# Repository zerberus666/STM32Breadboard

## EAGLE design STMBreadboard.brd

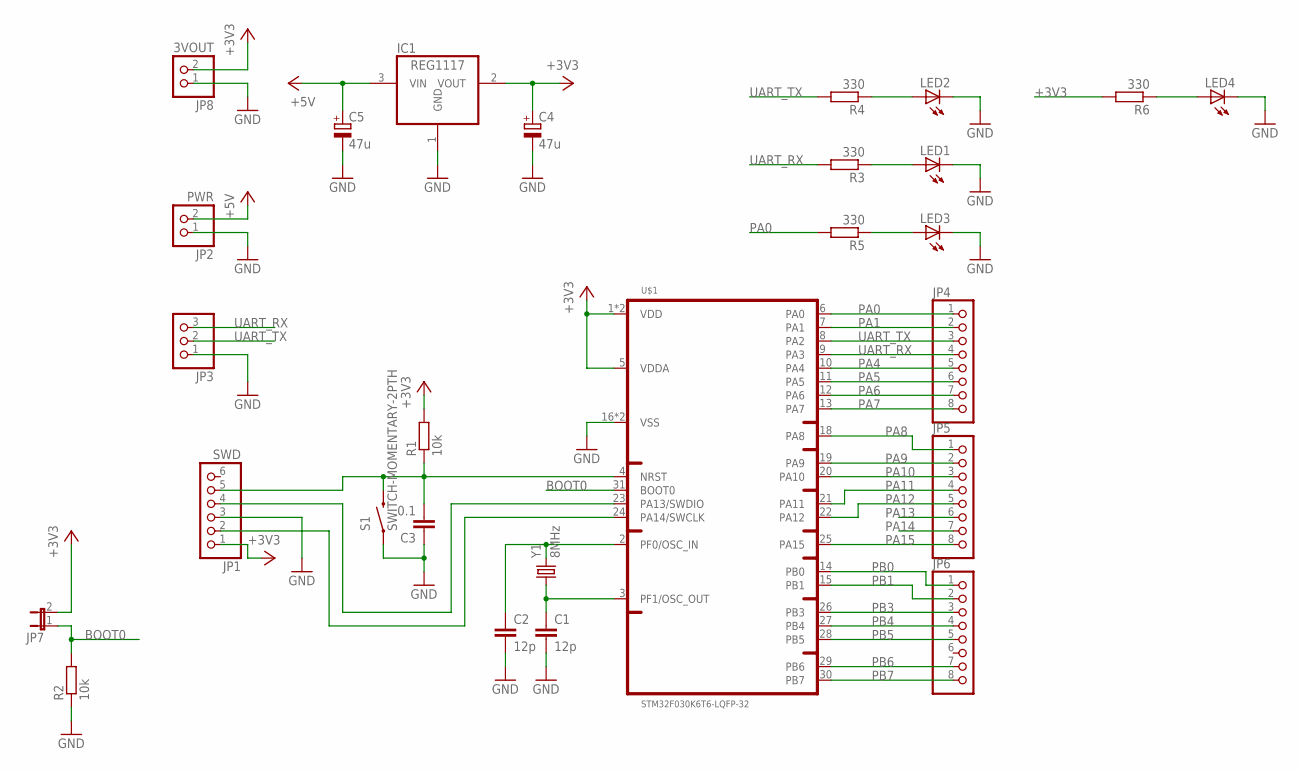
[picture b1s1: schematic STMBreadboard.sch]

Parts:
C1, C2: 12p; C0805
C3: 0.1; C0805
C4, C5: 47u; UD-6,3X7,7_NICHICON
IC1: REG1117; SOT223
JP1: SWD; 1X06
JP2: PWR; 1X02
JP3: PINHD-1X3; 1X03
JP4, JP5, JP6: PINHD-1X8; 1X08
JP7: JP1E; JP1
JP8: 3VOUT; 1X02
LED1, LED2: LEDCHIPLED_0603; CHIPLED_0603
LED3, LED4: LEDSML0603; SML0603
R1, R2: 10k; R1206
R3, R4, R5, R6: 330; R1206
S1: SWITCH-MOMENTARY-2PTH; TACTILE-PTH
U$1: STM32F030K6T6-LQFP-32; LQFP-32
Y1: 8MHz; HC49UP

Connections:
+3V3: C4.+, IC1.2 (VOUT), JP1.1, JP7.2, JP8.2, R1.2, R6.2, U$1.1 (VDD), U$1.5 (VDDA), U$1.17 (VDD)
+5V: C5.+, IC1.3 (VIN), JP2.2
BOOT0: JP7.1, R2.2, U$1.31 (BOOT0)
GND: C1.2, C2.2, C3.1, C4.-, C5.-, IC1.1 (GND), JP1.3, JP2.1, JP3.1, JP8.1, LED1.C, LED2.C, LED3.C, LED4.C, R2.1, S1.1, U$1.16 (VSS), U$1.32 (VSS)
unnamed: C2.1, U$1.2 (PF0/OSC_IN), Y1.2
unnamed: C1.1, U$1.3 (PF1/OSC_OUT), Y1.1
unnamed: C3.2, JP1.5, R1.1, S1.3 (2), U$1.4 (NRST)
unnamed: LED1.A, R3.1
unnamed: LED2.A, R4.1
unnamed: LED3.A, R5.1
unnamed: LED4.A, R6.1
PA0: JP4.1, R5.2, U$1.6 (PA0)
PA1: JP4.2, U$1.7 (PA1)
PA4: JP4.5, U$1.10 (PA4)
PA5: JP4.6, U$1.11 (PA5)
PA6: JP4.7, U$1.12 (PA6)
PA7: JP4.8, U$1.13 (PA7)
PA8: JP5.1, U$1.18 (PA8)
PA9: JP5.2, U$1.19 (PA9)
PA10: JP5.3, U$1.20 (PA10)
PA11: JP5.4, U$1.21 (PA11)
PA12: JP5.5, U$1.22 (PA12)
PA13: JP1.4, JP5.6, U$1.23 (PA13/SWDIO)
PA14: JP1.2, JP5.7, U$1.24 (PA14/SWCLK)
PA15: JP5.8, U$1.25 (PA15)
PB0: JP6.1, U$1.14 (PB0)
PB1: JP6.2, U$1.15 (PB1)
PB3: JP6.3, U$1.26 (PB3)
PB4: JP6.4, U$1.27 (PB4)
PB5: JP6.5, U$1.28 (PB5)
PB6: JP6.7, U$1.29 (PB6)
PB7: JP6.8, U$1.30 (PB7)
UART_RX: JP3.3, JP4.4, R3.2, U$1.9 (PA3)
UART_TX: JP3.2, JP4.3, R4.2, U$1.8 (PA2)

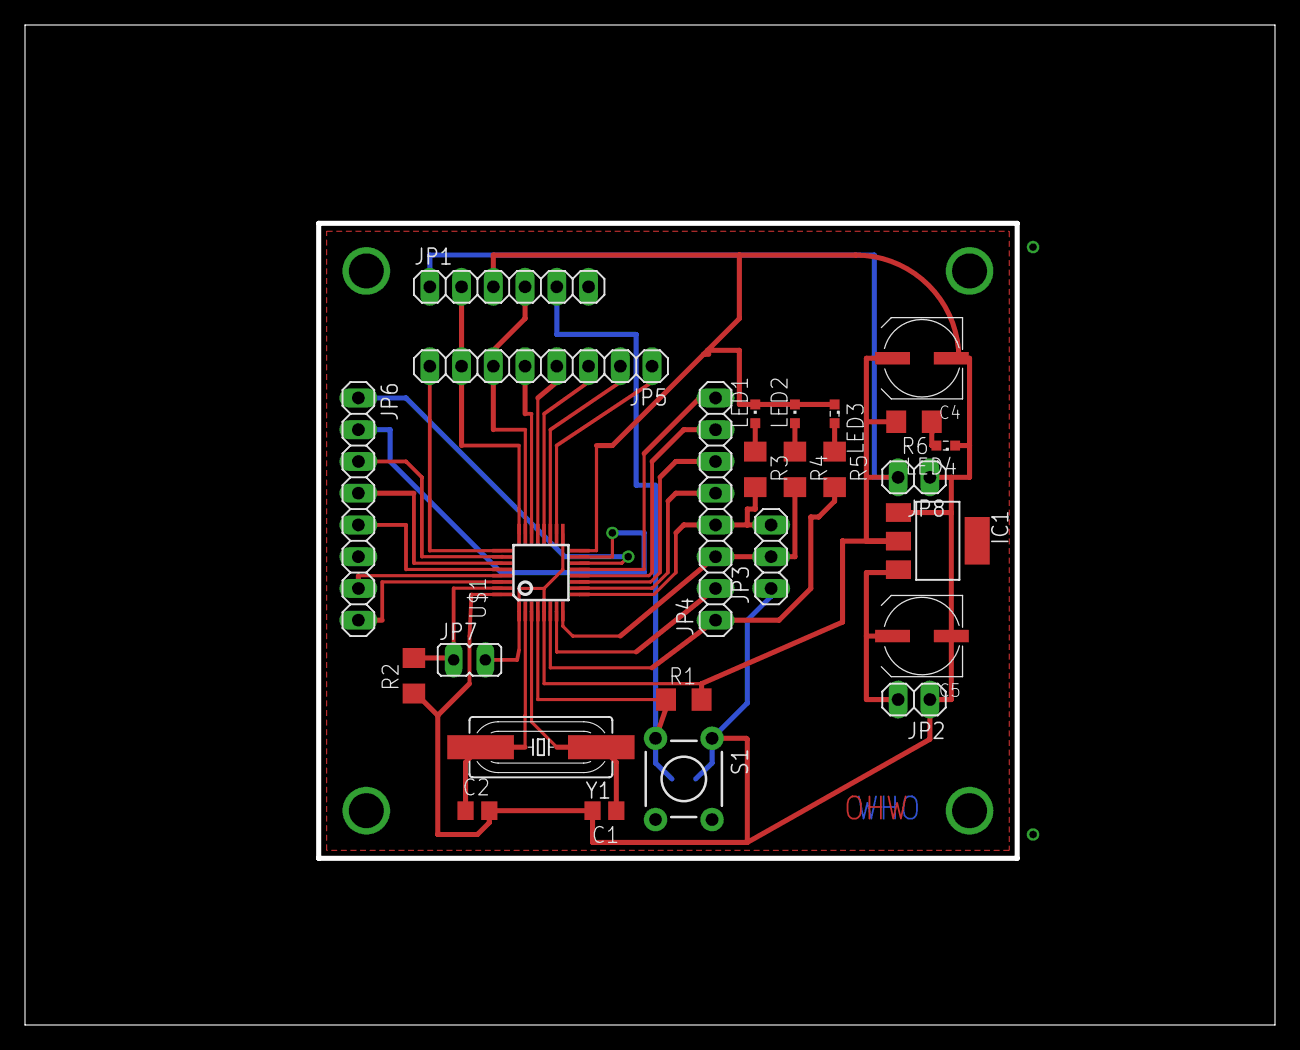
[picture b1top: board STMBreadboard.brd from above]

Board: 2 copper layers, 99.6 x 79.6 mm, 27 parts (1 on the bottom side), 34 nets.

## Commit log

2015-07-06 New breadboard STM32
2015-07-06 second
2015-07-06 PCB001
2015-07-07 PCB002
2015-07-07 PCB003
2015-07-07 PCB004
2015-07-17 LED 0603
2015-07-17 LED 0603-002
2015-07-17 readme md added
2015-07-17 inkscape PCB image for laser iron technology added
2015-07-17 inkscape PCB image for laser iron technology added002
2015-07-25 inkscape PCB image for laser iron technology changed
2015-08-12 Through holes
2015-08-12 eps pdf svg added
2015-08-12 PDF removed

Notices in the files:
parts and their libraries:
SparkFun-Electromechanical: Licensing: Creative Commons ShareAlike 4.0 International - https://creativecommons.org/licenses/by-sa/4.0
